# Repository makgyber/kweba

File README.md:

# @n

Another wireless keyboard

## Features

- 34 keys ortho split
- diodeless
- wireless using ZMK with nice!nano compatible controller
- optional reset and on/off switch

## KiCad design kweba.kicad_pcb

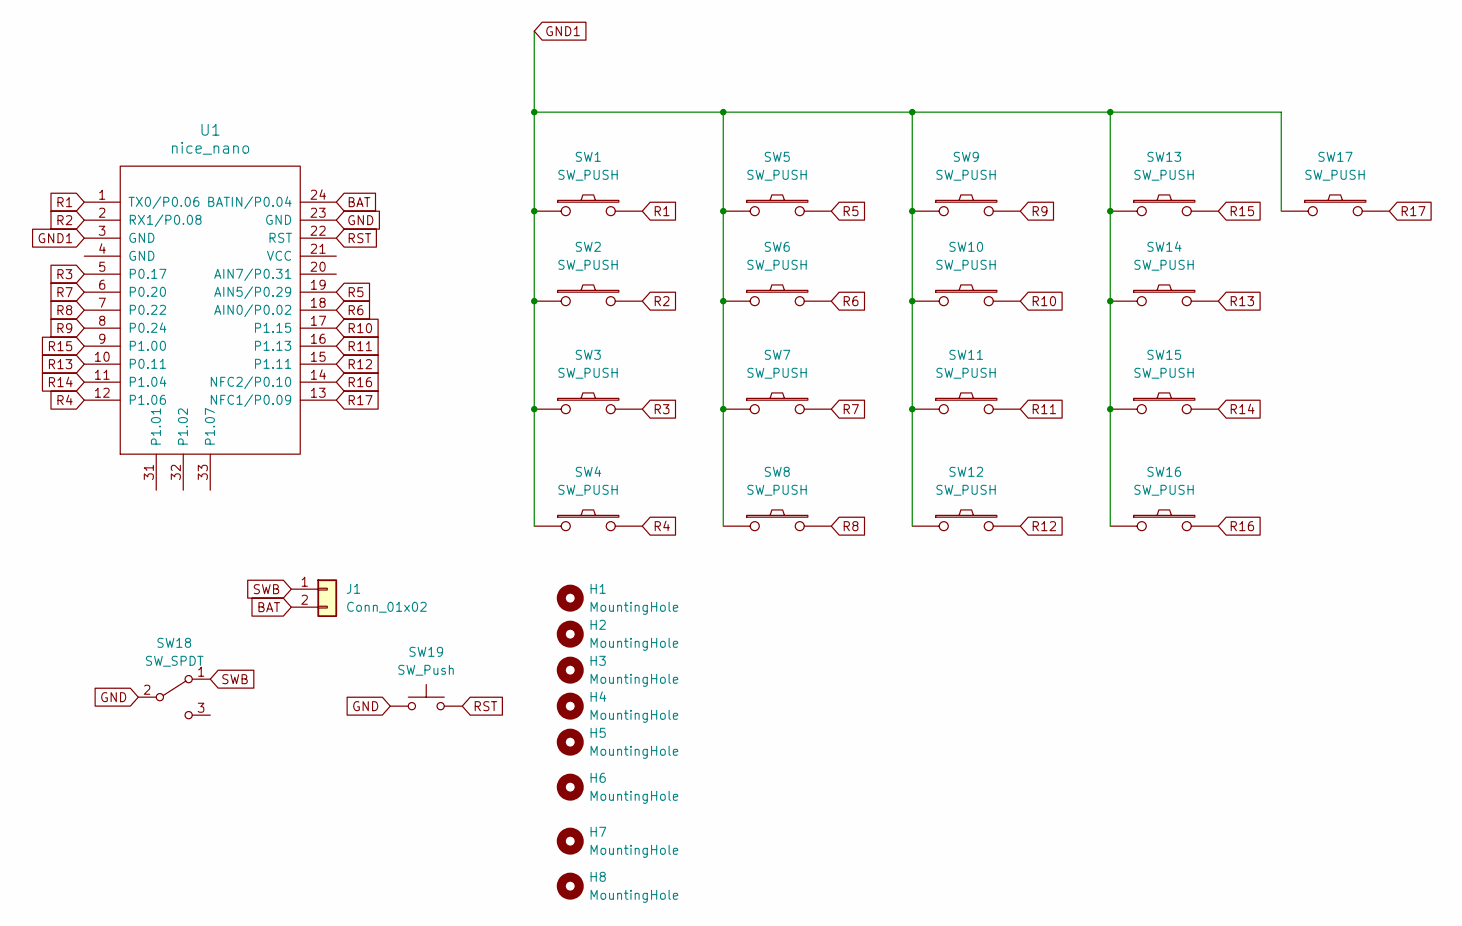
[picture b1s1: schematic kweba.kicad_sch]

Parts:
H1, H2, H3, H4, H5, H6, H7, H8: MountingHole; MountingHole_2.5mm
J1: Conn_01x02; JST_EH_B2B-EH-A_1x02_P2.50mm_Vertical
SW1, SW2, SW3, SW4, SW5, SW6, SW7, SW8, SW9, SW10, SW11, SW12, SW13, SW14, SW15, SW16, SW17: SW_PUSH; pg1350-R
SW18: SW_SPDT; SW_SPDT_PCM12
SW19: SW_Push; ResetSW
U1: nice_nano

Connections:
BAT: J1.2, U1.24 (BATIN/P0.04)
GND: SW18.2 (B), SW19.1, U1.23 (GND)
GND1: SW1.1, SW2.1, SW3.1, SW4.1, SW5.1, SW6.1, SW7.1, SW8.1, SW9.1, SW10.1, SW11.1, SW12.1, SW13.1, SW14.1, SW15.1, SW16.1, SW17.1, U1.3 (GND)
R1: SW1.2, U1.1 (TX0/P0.06)
R2: SW2.2, U1.2 (RX1/P0.08)
R3: SW3.2, U1.5 (P0.17)
R4: SW4.2, U1.12 (P1.06)
R5: SW5.2, U1.19 (AIN5/P0.29)
R6: SW6.2, U1.18 (AIN0/P0.02)
R7: SW7.2, U1.6 (P0.20)
R8: SW8.2, U1.7 (P0.22)
R9: SW9.2, U1.8 (P0.24)
R10: SW10.2, U1.17 (P1.15)
R11: SW11.2, U1.16 (P1.13)
R12: SW12.2, U1.15 (P1.11)
R13: SW14.2, U1.10 (P0.11)
R14: SW15.2, U1.11 (P1.04)
R15: SW13.2, U1.9 (P1.00)
R16: SW16.2, U1.14 (NFC2/P0.10)
R17: SW17.2, U1.13 (NFC1/P0.09)
RST: SW19.2, U1.22 (RST)
SWB: J1.1, SW18.1 (A)

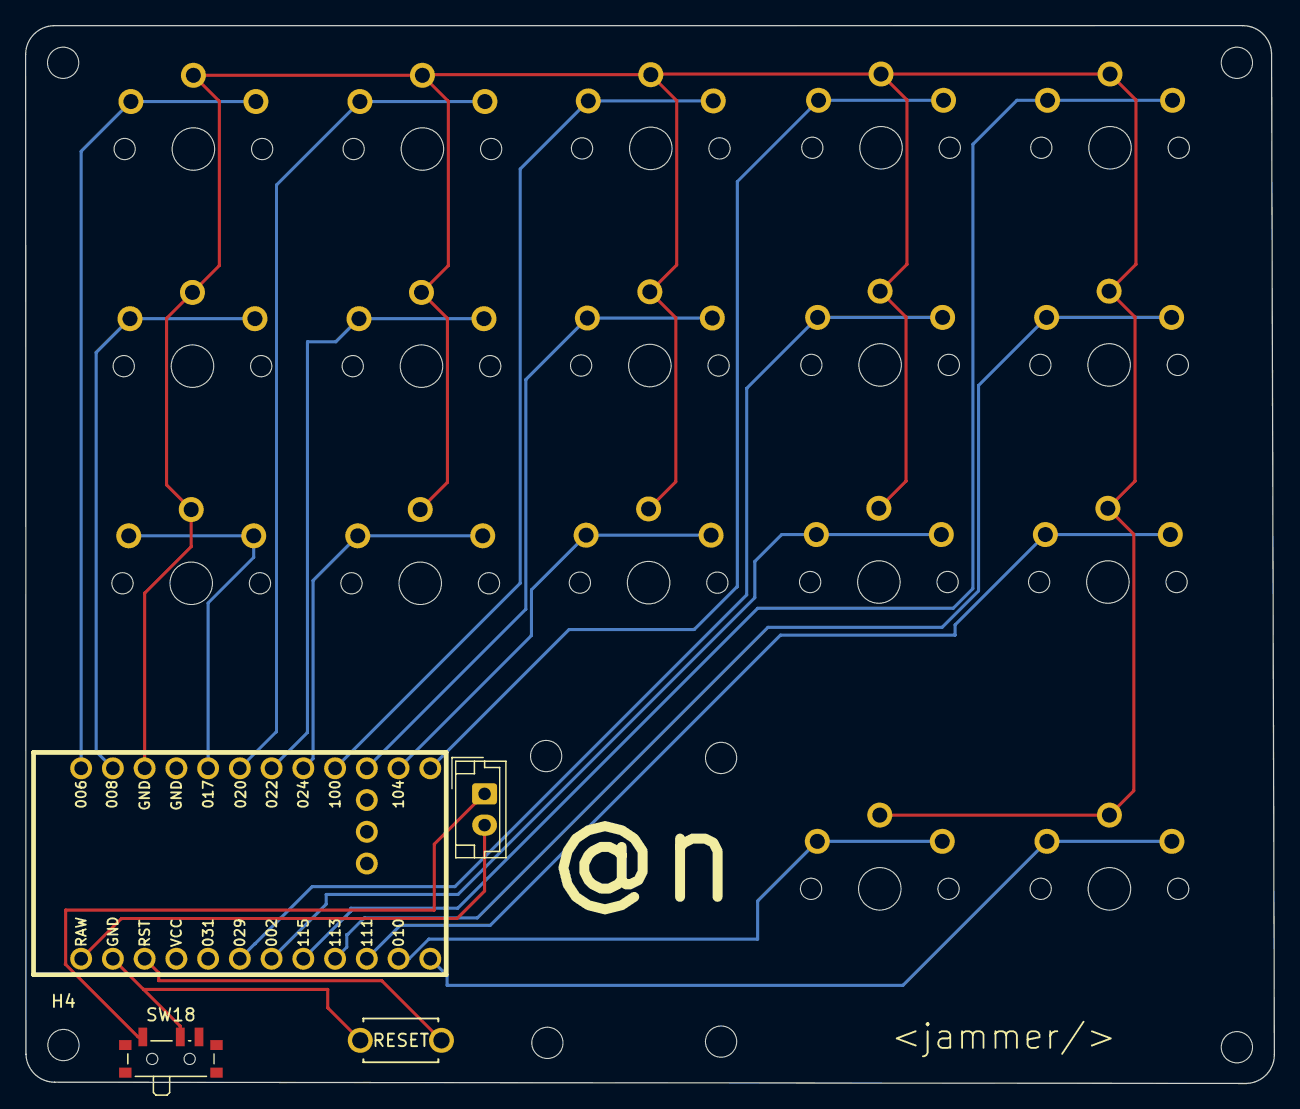
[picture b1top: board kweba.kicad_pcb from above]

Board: 2 copper layers, 99.9 x 84.6 mm, 29 parts (1 on the bottom side), 22 nets.

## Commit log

2024-11-04 readme
2025-08-27 update keymap
